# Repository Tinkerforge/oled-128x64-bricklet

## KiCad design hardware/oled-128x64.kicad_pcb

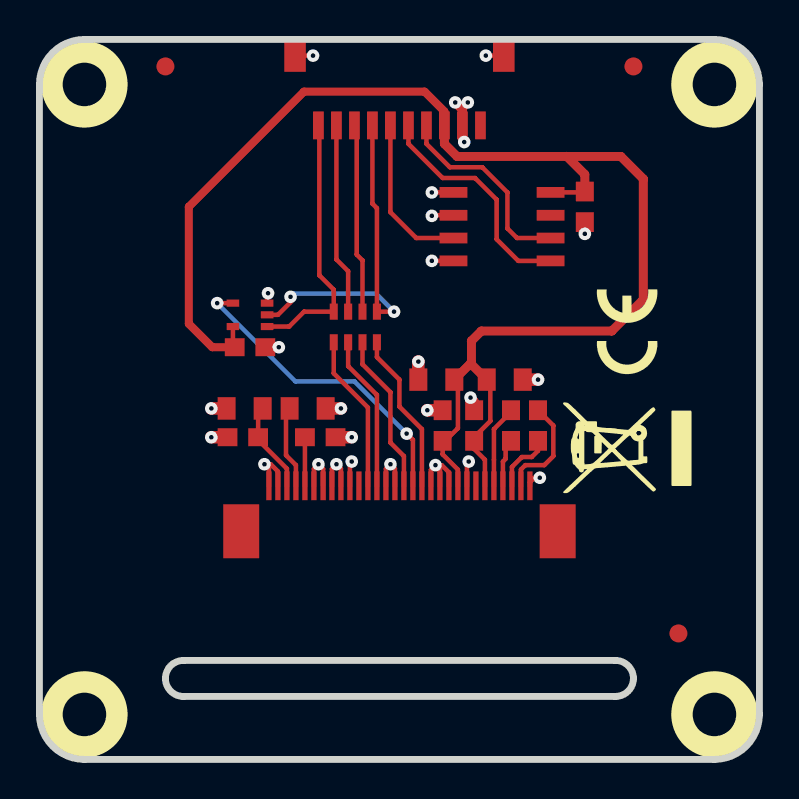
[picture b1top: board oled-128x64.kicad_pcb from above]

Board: 2 copper layers, 40.0 x 40.0 mm, 25 parts (0 on the bottom side), 21 nets.

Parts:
C1, C2, C4, C6, C11: 100nF; C0603E
C3, C5, C7: 4.7µF/25V; C0805
C8, C10: 1µF; C0603E
C9: 10µF; C0805
Fiducial_Mark: VAL**; Fiducial_Mark
Fiducial_Mark#2, Fiducial_Mark#3: VAL**; Fiducial_Mark
P1: CON-SENSOR
R1: 390k; R0603E
RP1: 2k2; 0603X4
U1: M24C64; SOIC8
U2: SNGL_NAND; SC70-5
U3: OLED013; ER-CON30HT-1
U4, U5, U6, U7: DRILL; DRILL_NP
VAL: CE_5mm

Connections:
3V3: C1.2, C2.2, C3.2, C4.2, C5.2, C6.2, P1.3, U1.8, U2.5, U3.6, U3.9
GND: C1.1, C2.1, C3.1, C4.1, C5.1, C6.1, C7.1, C9.1, C11.1, P1.2, P1.EP, R1.2, U1.1, U1.2, U1.4, U2.3, U3.1, U3.8, U3.10, U3.11, U3.12, U3.16, U3.17, U3.21, U3.22, U3.23, U3.24, U3.25, U3.29, U3.30
unnamed: C7.2, U3.27
unnamed: C8.1, U3.5
unnamed: C8.2, U3.4
unnamed: C10.1, U3.3
unnamed: C10.2, U3.2
unnamed: C9.2, C11.2, U3.28
unnamed: P1.4, U1.6
unnamed: P1.5, U1.5
unnamed: P1.6, U1.3
unnamed: P1.7, RP1.1, U2.2
unnamed: P1.8, RP1.2
unnamed: P1.9, RP1.3
unnamed: P1.10, RP1.4, U2.1
unnamed: R1.1, U3.26
unnamed: RP1.5, U3.19
unnamed: RP1.6, U3.18
unnamed: RP1.7, U3.15
unnamed: RP1.8, U3.13
unnamed: U2.4, U3.14

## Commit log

2015-06-19 first prototype of oled 128x64 Bricklet
2015-06-19 connect nc pins with gnd
2015-06-19 change dimensions
2015-06-21 fix cutout position for lcd cable
2015-06-21 fix gnd layer
2015-06-22 Add Datasheets
2015-06-22 put module description to the front
2015-06-25 add i2c pullup
2015-06-25 change to 4-wire SPI
2015-06-25 change schamtic to 3-wire spi
2015-06-29 add nand for reset line
2015-07-10 Add Implementation for 128x64
2015-07-13 Add .gitignore
2015-07-23 Updating .gitignore to ignore eclipse related files
2015-07-23 Adding Python examples
2015-07-27 Cleanup Python examples
2015-07-29 Reformat changelog
2015-07-31 Consistent UID and better variable name
2015-07-31 Calculate value from constant
2015-07-31 Adding C/C++ examples
2015-08-03 Some fixes on C pixel matrix example
2015-08-03 Adding C# examples
2015-08-03 Adding Delphi examples
2015-08-03 Adding Java examples
2015-08-03 Adding JavaScript examples
2015-08-03 Adding MATLAB examples
2015-08-03 Adding Perl examples
2015-08-03 Adding PHP examples
2015-08-03 Python 3 compatibility
2015-08-03 Adding Ruby examples
2015-08-03 Adding Shell examples
2015-08-03 Remove dot slash
2015-08-03 Adding VB.NET examples
2015-08-07 Use full device class name in Python examples
2015-08-12 Fix minor warnings in C/C++ examples
2015-08-14 Fix typo
2015-08-17 Cleanup Delphi example
2015-08-18 Whitespace
2015-08-18 Use correct Bricklet class in VB.NET example
2015-08-19 Cleanup Perl examples
2015-08-24 change pullup to series resistor, fix routing
2015-09-09 Duplicate cmake call to fix bug during cmake creation
2015-09-17 add hardware version number
2015-10-20 drc check
2015-10-21 Generator based example cleanup
2015-11-12 matlab: Fix callback handling for R2014a
    http://undocumentedmatlab.com/blog/matlab-callbacks-for-java-events-in-r2014a
2015-11-25 Include date and commit into changelog
2016-01-05 Use better checkerboard pattern in examples
2016-01-05 Add Mathematica examples
2016-01-05 Add LabView examples
2016-01-05 python: Get image from command line
2016-01-06 vbnet: Fix strict type warnings
2016-01-06 add schematic pdf
2016-01-07 Remove WIP marker
2016-01-11 Update changelog
2016-01-11 Add Servo/Poti example
2016-01-11 Add free-form drawing example for C#, Java and Python
2016-01-13 Add JavaScript (Node.js) example
2016-01-13 Some example logic cleanup
2016-01-14 Add VB.NET scribble example
2016-01-14 Add Perl scribble examples
2016-01-14 Add PHP scribble example
2016-01-14 Add Ruby scribble example
2016-01-14 Add C scribble example
2016-01-14 delphi: Fix array slicing
2016-01-28 vbnet: Use integer division
2016-02-08 Start extending examples to deal with different window sizes and positions
2016-02-08 perl: Fix warning
2016-02-09 vbnet: Fix compiler warning
2016-05-18 c: Add missing device destroy call
2016-06-17 oled version 1.1 * add connector for display
2016-07-01 Make the change UID comment more explicit
2017-06-02 octave: Use javaObject instead of deprecated java_new
2017-10-13 Add 3d information (tbc)
2017-10-23 Add 3d information (final)
2017-10-23 Add 3d models (*.step & *.FCStd)
2017-12-07 mathematica: Also generate .nb files
2018-02-19 javascript: Close div tag correctly
2018-02-20 Cleanup KiCad libraries config
    Ensure LibDir=kicad-libraries and LibName1=tinkerforge.
    Remove special library.
2018-05-24 perl: Use strict in examples
2018-07-11 Add Makefile with docker support
2018-07-11 Update directory structure and build instructions
2018-07-11 Remove obsolete generate_makefile scripts
2018-09-06 Add font render script
2018-11-06 Add rust examples
2018-11-07 rust: Accept host names for ip connection, fix naming inconsistencies
2018-12-04 rust: Fix pixel matrix example.
2018-12-04 rust: Really fix pixel matrix example.
2018-12-04 rust: Fix pixel matrix example again.
2018-12-14 Add go examples.
2018-12-18 go: Change import path.
2018-12-18 go: Change import path again.
2018-12-20 rust: Reformat examples.
2019-01-24 mqtt: Add examples.
2019-01-24 mqtt: Fix example header.
2019-01-24 mqtt: Remove executable bit in example permissions.
2019-01-24 go: Minor example fixes.
2019-01-24 mqtt: Minor example fixes.
2019-08-13 Add updated font editor
2020-01-13 examples: Use python3 input instead of python2 raw_input.
2020-01-13 examples: mqtt: Remove trailing whitespace.
2020-01-14 examples: Use python3 input by default.
2020-02-26 examples: Update "Change UID" comment style
2020-03-18 rust: Update to new skeleton
2020-04-07 examples: rust: Always block when calling bindings functions.
2021-10-25 Update KiCad link
    https://www.kicad.org/blog/2021/10/Avoid-links-to-former-kicad-domain/
2022-03-07 Add code page 437 hint
2022-07-06 Add license files.
2024-02-23 vbnet: Fix for loops

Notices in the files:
hardware/oled-128x64.kicad_pcb:
Licensed under CERN OHL v.1.1
Copyright (©) 2016, B.Nordmeyer
